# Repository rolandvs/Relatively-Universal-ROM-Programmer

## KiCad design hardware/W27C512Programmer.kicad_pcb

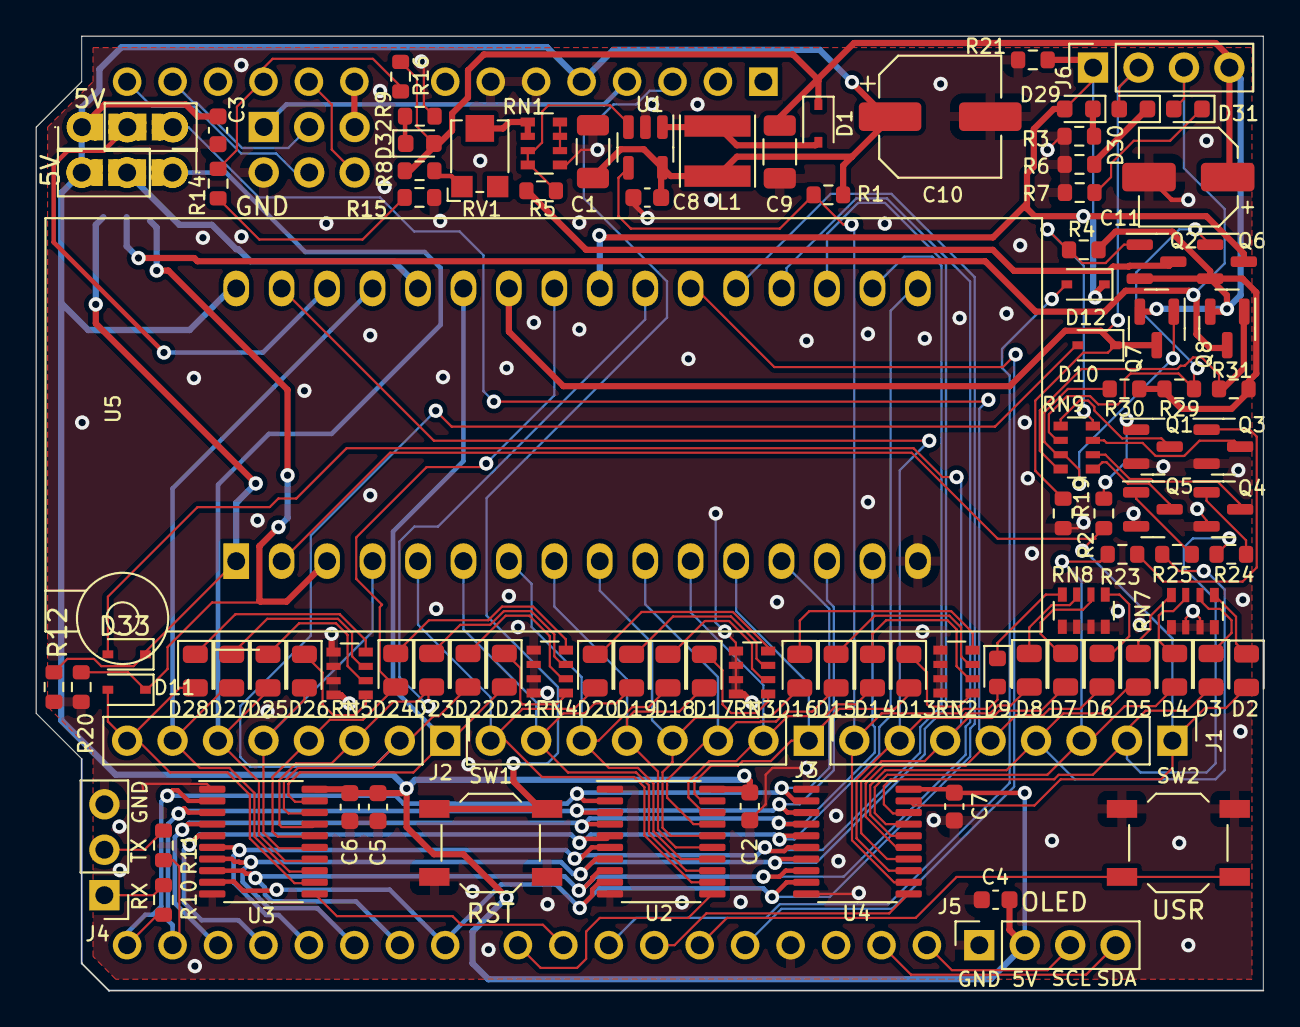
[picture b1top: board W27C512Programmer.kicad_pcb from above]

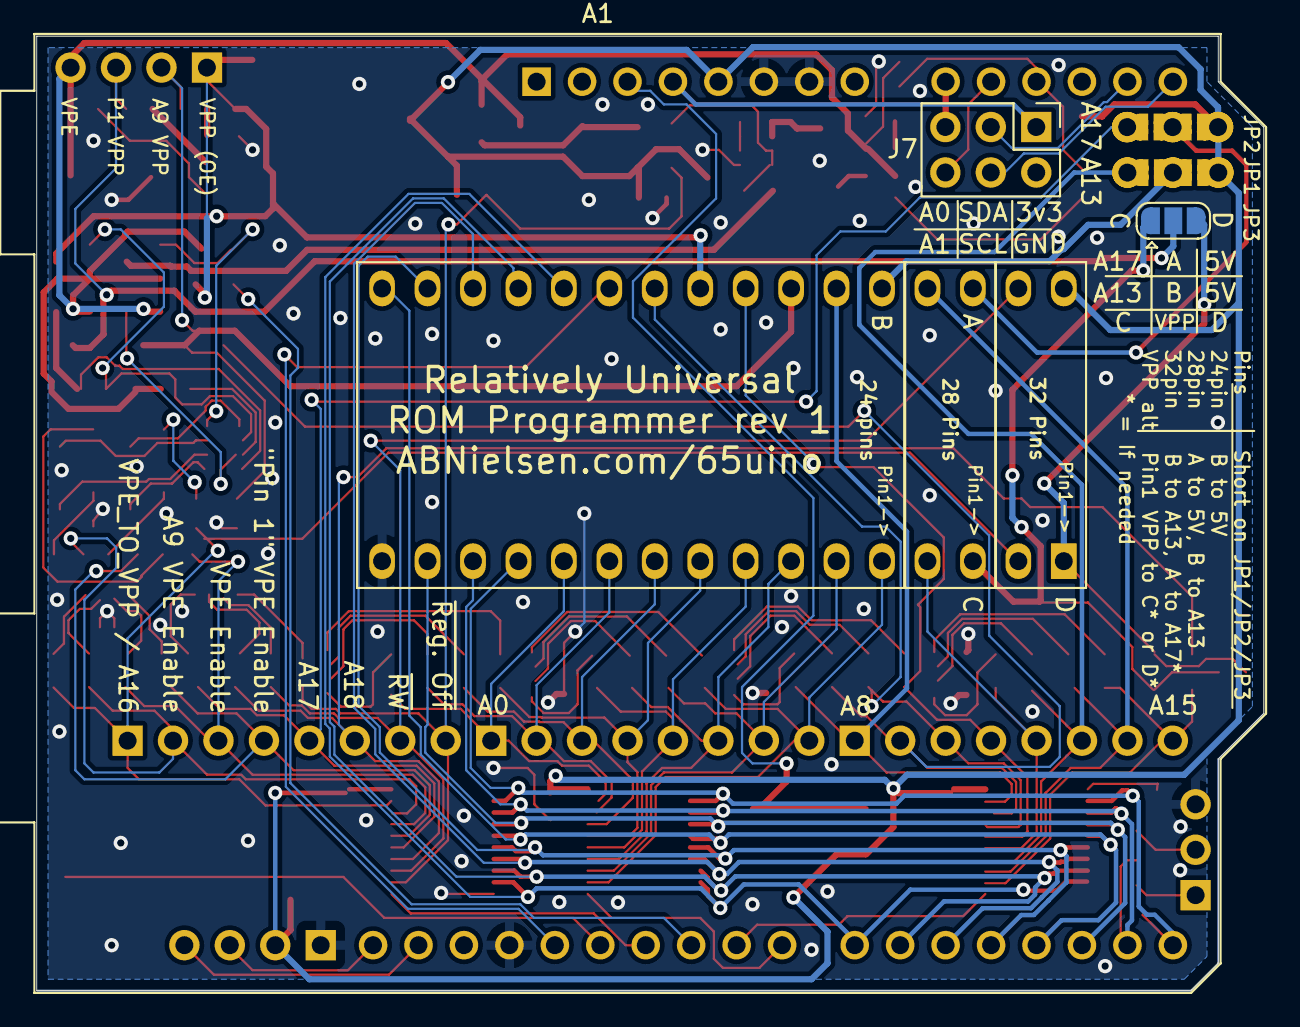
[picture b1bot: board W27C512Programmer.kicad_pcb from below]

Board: 2 copper layers, 68.6 x 53.3 mm, 104 parts (3 on the bottom side), 106 nets.

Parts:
A1: Arduino_UNO_R3
C1, C9: 10uF; C_1206_3216Metric
C2, C3, C4, C5, C6, C7, C8: 100nF; C_0603_1608Metric
C10: 220uF; CP_Elec_6.3x5.4
C11: NC; CP_Elec_5x5.4
D1, D10, D11, D12, D33: 1N5819; D_SOD-323
D2, D3, D4, D5, D6, D7, D8, D13, D14, D15, D16, D17, D18, D19, D20, D21, D22, D23, D24, D25, D26, D27, D28: GREEN; LED_0805_2012Metric
D9, D29, D30, D31, D32: RED; LED_0603_1608Metric
J1: CTRL; PinHeader_1x08_P2.54mm_Vertical
J2: MSB; PinHeader_1x08_P2.54mm_Vertical
J3: LSB; PinHeader_1x08_P2.54mm_Vertical
J4: Ext_UART; PinHeader_1x03_P2.54mm_Vertical
J5: OLED; PinSocket_1x04_P2.54mm_Vertical
J6: VP; PinSocket_1x04_P2.54mm_Vertical
J7: SAO; PinHeader_2x03_P2.54mm_Vertical
JP1: 24pin ROM VCC; PinHeader_1x03_P2.54mm_Vertical_SolderJumpers
JP2: >=SST39SF020 & 28C512 need A17; PinHeader_1x03_P2.54mm_Vertical_SolderJumpers
JP3: W27C010/AT27C010 needs p1 VPE/VPP (32 pin); SolderJumper-3_P1.3mm_Open_RoundedPad1.0x1.5mm
L1: 10uH; L_Taiyo-Yuden_MD-4040
Q1, Q3, Q4, Q5: MMBT3904; SOT-23
Q2, Q6, Q7, Q8: MMBT3906; SOT-23
R1, R2, R3, R4, R6, R7, R8, R9, R12, R14, R15, R19, R20, R21, R23, R24, R25, R29, R30, R31: 22k; R_0603_1608Metric
R5, R16: 270k; R_0603_1608Metric
R10, R11: 1k; R_0603_1608Metric
RN1, RN2, RN3, RN4, RN5, RN7, RN8, RN9: 4k7; R_Array_Convex_4x0603
RV1: 50k; Potentiometer_Bourns_TC33X_Vertical
SW1: RST; SW_SPST_TL3342
SW2: USR; SW_SPST_TL3342
U1: MIC2288; SOT-23-5
U2, U3, U4: 74HC573; TSSOP-20_4.4x6.5mm_P0.65mm
U5: 28/32 pin ROM; DIP_Socket-32_W11.9_W12.7_W15.24_W17.78_W18.5_3M_232-1285-0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

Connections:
+5V: A1.5 (+5V), C1.1, C2.1, C3.1, C4.1, C5.1, C6.1, C7.1, C8.1, C10.1, J5.2, JP1.3 (B), JP2.1 (A), L1.1, R1.1, U1.5 (IN), U2.20 (VCC), U3.20 (VCC), U4.20 (VCC), U5.32 (VCC)
/A0: D13.2 (A), J3.1, U2.19 (Q0), U5.12 (A0)
/A1: D14.2 (A), J3.2, U2.18 (Q1), U5.11 (A1)
/A2: D15.2 (A), J3.3, U2.17 (Q2), U5.10 (A2)
/A3: D16.2 (A), J3.4, U2.16 (Q3), U5.9 (A3)
/A4: D17.2 (A), J3.5, U2.15 (Q4), U5.8 (A4)
/A5: D18.2 (A), J3.6, U2.14 (Q5), U5.7 (A5)
/A6: D19.2 (A), J3.7, U2.13 (Q6), U5.6 (A6)
/A7: D20.2 (A), J3.8, U2.12 (Q7), U5.5 (A7)
/A8: D21.2 (A), J2.1, U3.19 (Q0), U5.27 (A8)
/A9: D10.2 (A), D22.2 (A), J2.2, U3.18 (Q1)
/A10: D23.2 (A), J2.3, U3.17 (Q2), U5.23 (A10)
/A11: D24.2 (A), J2.4, U3.16 (Q3), U5.25 (A11)
/A12: D25.2 (A), J2.5, U3.15 (Q4), U5.4 (A12)
/A13: D26.2 (A), J2.6, JP1.1 (A), U3.14 (Q5)
/A14: D27.2 (A), J2.7, U3.13 (Q6), U5.29 (A14)
/A15: D11.2 (A), D28.2 (A), J2.8, U3.12 (Q7)
A9_VPP_ENABLE: D3.2 (A), J1.2, R24.1, U4.18 (Q1)
A16: D2.2 (A), J1.1, R2.1, U4.19 (Q0), U5.2 (A16)
A17: D6.2 (A), J1.5, JP2.3 (B), U4.15 (Q4)
A18: D7.2 (A), D33.2 (A), J1.6, U4.14 (Q5)
CTRL_LE: A1.26 (D11), U4.11 (Load)
D0: A1.15 (D0/RX), R10.2, U2.2 (D0), U3.2 (D0), U4.2 (D0), U5.13 (D0)
D1: A1.16 (D1/TX), R11.2, U2.3 (D1), U3.3 (D1), U4.3 (D1), U5.14 (D1)
D2: A1.17 (D2), U2.4 (D2), U3.4 (D2), U4.4 (D2), U5.15 (D2)
D3: A1.18 (D3), U2.5 (D3), U3.5 (D3), U4.5 (D3), U5.17 (D3)
D4: A1.19 (D4), U2.6 (D4), U3.6 (D4), U4.6 (D4), U5.18 (D4)
D5: A1.20 (D5), U2.7 (D5), U3.7 (D5), U4.7 (D5), U5.19 (D5)
D6: A1.21 (D6), U2.8 (D6), U3.8 (D6), U4.8 (D6), U5.20 (D6)
D7: A1.22 (D7), U2.9 (D7), U3.9 (D7), U4.9 (D7), U5.21 (D7)
GND: A1.6 (GND), A1.7 (GND), A1.29 (GND), C1.2, C2.2, C3.2, C4.2, C5.2, C6.2, C7.2, C8.2, C9.2, C10.2, C11.2, J4.3, J5.1, J7.2, Q1.2 (E), Q3.2 (E), Q4.2 (E), Q5.2 (E), R3.2, R6.2, R7.2, R9.2, R12.2, R15.2, R19.2, R20.2, R21.2, RN1.5 (R4.2), RN2.1 (R1.1), RN2.2 (R2.1), RN2.3 (R3.1), RN2.4 (R4.1), RN3.1 (R1.1), RN3.2 (R2.1), RN3.3 (R3.1), RN3.4 (R4.1), RN4.1 (R1.1), RN4.2 (R2.1), RN4.3 (R3.1), RN4.4 (R4.1), RN5.1 (R1.1), RN5.2 (R2.1), RN5.3 (R3.1), RN5.4 (R4.1), RN7.1 (R1.1), RN7.2 (R2.1), RN7.3 (R3.1), RN7.4 (R4.1), RN8.1 (R1.1), RN8.2 (R2.1), RN8.3 (R3.1), RN8.4 (R4.1), SW1.2, SW2.1, U1.2 (GND), U2.1 (OE), U2.10 (GND), U3.1 (OE), U3.10 (GND), U4.1 (OE), U4.10 (GND), U5.16 (GND)
unnamed: A1.3 (~RESET), SW1.1
unnamed: A1.4 (3V3), J7.1
unnamed: A1.9 (A0), J7.5
unnamed: A1.10 (A1), J7.6
unnamed: A1.27 (D12), SW2.2
unnamed: D1.2 (A), L1.2, U1.1 (SW)
unnamed: D2.1 (K), RN7.5 (R4.2)
unnamed: D3.1 (K), RN7.6 (R3.2)
unnamed: D4.1 (K), RN7.7 (R2.2)
unnamed: D5.1 (K), RN7.8 (R1.2)
unnamed: D6.1 (K), RN8.5 (R4.2)
unnamed: D7.1 (K), RN8.6 (R3.2)
unnamed: D8.1 (K), RN8.7 (R2.2)
unnamed: D9.1 (K), RN8.8 (R1.2)
unnamed: D10.1 (K), D30.2 (A), J6.2, Q7.3 (C), R19.1, U5.26 (A9)
unnamed: D11.1 (K), JP3.1 (A), R20.1, U5.3 (A15)
unnamed: D12.1 (K), D29.2 (A), J6.1, Q6.3 (C), R21.1, U5.24 (OE)
unnamed: D13.1 (K), RN2.5 (R4.2)
unnamed: D14.1 (K), RN2.6 (R3.2)
unnamed: D15.1 (K), RN2.7 (R2.2)
unnamed: D16.1 (K), RN2.8 (R1.2)
unnamed: D17.1 (K), RN3.5 (R4.2)
unnamed: D18.1 (K), RN3.6 (R3.2)
unnamed: D19.1 (K), RN3.7 (R2.2)
unnamed: D20.1 (K), RN3.8 (R1.2)
unnamed: D21.1 (K), RN4.5 (R4.2)
unnamed: D22.1 (K), RN4.6 (R3.2)
unnamed: D23.1 (K), RN4.7 (R2.2)
unnamed: D24.1 (K), RN4.8 (R1.2)
unnamed: D25.1 (K), RN5.5 (R4.2)
unnamed: D26.1 (K), RN5.6 (R3.2)
unnamed: D27.1 (K), RN5.7 (R2.2)
unnamed: D28.1 (K), RN5.8 (R1.2)
unnamed: D29.1 (K), R3.1
unnamed: D30.1 (K), R6.1
unnamed: D31.1 (K), R7.1
unnamed: D31.2 (A), J6.3, JP3.2 (C), Q8.3 (C)
unnamed: D32.1 (K), R9.1
unnamed: D33.1 (K), JP3.3 (B), R12.1, U5.1 (A18)
unnamed: J4.1, R10.1
unnamed: J4.2, R11.1
unnamed: JP1.2 (C), U5.28 (A13)
unnamed: JP2.2 (C), U5.30 (A17)
unnamed: Q1.1 (B), R2.2
unnamed: Q1.3 (C), RN9.1 (R1.1)
unnamed: Q2.1 (B), R4.2, RN9.8 (R1.2)
unnamed: Q2.3 (C), R5.1
unnamed: Q3.1 (B), R23.2
unnamed: Q3.3 (C), RN9.7 (R2.2)
unnamed: Q4.1 (B), R24.2
unnamed: Q4.3 (C), RN9.6 (R3.2)
unnamed: Q5.1 (B), R25.2
unnamed: Q5.3 (C), RN9.5 (R4.2)
unnamed: Q6.1 (B), R29.2, RN9.2 (R2.1)
unnamed: Q7.1 (B), R30.2, RN9.3 (R3.1)
unnamed: Q8.1 (B), R31.2, RN9.4 (R4.1)
unnamed: R5.2, RN1.3 (R3.1), RN1.4 (R4.1), U1.3 (FB)
unnamed: R8.2, RV1.1
unnamed: R14.1, R15.1
unnamed: A1.11 (A2), R14.2, R16.2
unnamed: RN1.1 (R1.1), RN1.2 (R2.1), RV1.2
unnamed: RN1.6 (R3.2), RN1.7 (R2.2), RN1.8 (R1.2)
P1_VPP_ENABLE: D5.2 (A), J1.4, R25.1, U4.16 (Q3)
RLSBLE: A1.23 (D8), U2.11 (Load)
RMSBLE: A1.24 (D9), U3.11 (Load)
SCL: A1.32 (SCL/A5), J5.3
SCL2: A1.14 (SCL/A5), J7.4
SDA: A1.31 (SDA/A4), J5.4
SDA2: A1.13 (SDA/A4), J7.3
VPE: C9.1, C11.1, D1.1 (K), D32.2 (A), J6.4, Q2.2 (E), Q6.2 (E), Q7.2 (E), Q8.2 (E), R4.1, R8.1, R16.1, R29.1, R30.1, R31.1
VPE_ENABLE: D4.2 (A), J1.3, R23.1, U4.17 (Q2)
~REG_DISABLE: D9.2 (A), J1.8, R1.2, U1.4 (~SHDN), U4.12 (Q7)
~ROM_CE: A1.28 (D13), U5.22 (CE)
~ROM_OE: A1.25 (D10), D12.2 (A)
~RW: D8.2 (A), J1.7, U4.13 (Q6), U5.31 (PGM)

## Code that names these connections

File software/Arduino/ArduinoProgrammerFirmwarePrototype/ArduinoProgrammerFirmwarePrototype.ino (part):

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const float V_REF = 5.06; // Reference voltage in volts
const int ANALOG_PIN = A2; // Analog pin connected to VEP

#define RLSBLE  0x01
#define RMSBLE  0x02
#define ROM_OE  0x04
#define CTRL_LE 0x08
#define USRBTN  0x10
#define ROM_CE  0x20

#define VPE_TO_VPP    0b00000001
#define A9_VPP_ENABLE 0b00000010
#define VPE_ENABLE    0b00000100
#define P1_VPP_ENABLE 0b00001000
#define A17_E         0b00010000
#define VCC28PIN      0b00010000
#define A18_E         0b00100000
#define RW            0b01000000
#define REG_DISABLE   0b10000000

uint32_t romsize = 4096; //We need to support more than 16 address bits
byte pattern = 0xAA;
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  PORTB |= RLSBLE | RMSBLE | ROM_OE | CTRL_LE | ROM_CE | USRBTN;
delayMicroseconds(1);
  // Set all latch pins LOW using direct port manipulation
  PORTB &= ~(RLSBLE | RMSBLE | CTRL_LE); // Set pins D8, D9, D11 low

    // Initialize the OLED display
  if(!display.begin(SSD1306_SWITCHCAPVCC, 0x3C)) {
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  display.println("Boot complete.");
  display.display();
  readAddress(0); //Init address latch
  latchControlByte(VCC28PIN|P1_VPP_ENABLE); //Can't latch things when serial is enabled
  delay(1); //Avoid serial framing error
  Serial.begin(baudrate);

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        Serial.end();
        if (rompincount == 24) {
        latchAddress(0x2000); //Enable VCC
        controlbyte = (REG_DISABLE | P1_VPP_ENABLE); //Enabling P1_VPP_Enable for JP4 (Leave OPEN for 28 pin ROMs!!))
        PORTB &= ~(ROM_CE); //Make sure chip is enabled
        }
        if (rompincount == 28) {
          controlbyte = (VPE_TO_VPP | REG_DISABLE | VPE_ENABLE | VCC28PIN);
        }

        display.clearDisplay();
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        display.print("Blocksize: ");
        display.print(currentCommand.blockSize);
        display.display();
        latchControlByte((VPE_TO_VPP | REG_DISABLE | VCC28PIN ) & controlbyte);
        delay(50); //Settle before enabling
        latchControlByte(controlbyte); //Burn ROM config
        delay(200);
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latchAddress(address);
byte controlbyte = 0;
        if (rompincount == 24) {
        controlbyte = (REG_DISABLE | P1_VPP_ENABLE); //Enabling P1_VPP_Enable for JP4 (Leave OPEN for 28 pin ROMs!!))
        }
        if (rompincount == 28) {
          controlbyte = (VPE_TO_VPP | REG_DISABLE | VPE_ENABLE | VCC28PIN);
        }

latchControlByte((VPE_TO_VPP | REG_DISABLE) & controlbyte);
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  DDRD  = 0xFF ; // All output
  PORTD = controlByte;

// Set CTRL_LE pin HIGH to latch
  PORTB |= CTRL_LE;
  // Set CTRL_LE pin LOW to unlatch
  PORTB &= ~(CTRL_LE);
}

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  if (lsb != prevLSB) {
    // Write LSB to PORTD
    PORTD = lsb;
    // Set CTRL_LE pin HIGH to latch lower 8 bits of address (LSB)
    PORTB |= RLSBLE;
    // Set RLSBLE pin LOW to unlatch lower 8 bits of address (LSB)
    PORTB &= ~RLSBLE;
    // Update prevLSB
    prevLSB = lsb;
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    }
    // Write MSB to PORTD
    PORTD = msb;
    // Set RMSBLE pin HIGH to latch higher 8 bits of address (MSB)
    PORTB |= RMSBLE;
    // Set RMSBLE pin LOW to unlatch higher 8 bits of address (MSB)
    PORTB &= ~RMSBLE;
    // Update prevMSB
    prevMSB = msb;
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
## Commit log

2024-05-19 Refactored SCH and bring up to KICAD 8.x
    - Schematic changed from A4 to A3
    - Reorganized schematic for better readability
    - Loaded SCH/PCB so KiCAD uses latest format
2025-08-17 2716 / TMS2532 support
    *ROM pin count must now be specified when calling the python scripts - this will turn on the VCC drivers.
    *Support for TMS2516 and M2716
2025-11-28 Improve 2716 support, structural improvements, standardised conventions and commentary (#18)
    * Fix multiple issues in ROM burner logic and improve reliability
    void latchAddress:
    - Update prevMSB before ORing in VCC for 24-pin ROMs; prevents msb != prevMSB always being true
    void writeFromBuffer:
    - For 24-pin chips, set CE low initially so 2716 can be processed first and CE returns low afterwards
    - Fix missing == operator in 28-pin condition

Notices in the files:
software/Arduino/ArduinoProgrammerFirmwarePrototype/ArduinoProgrammerFirmwarePrototype.ino:
Some GPL license
